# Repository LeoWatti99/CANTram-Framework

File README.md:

# CAN-TRAM-Framework
Das CAN-TRAM-Framework ist ein mikrocontrollerbasiertes, modulares Steuerungssystem, dass sich aus einzelnen Modulen zusammensetzen lässt. Die Struktur des Systems orientiert sich an üblichen SPS-Systemen, sodass eine CPU bzw. ein Hauptmodul um beliebig viele Module erweitert werden kann, um Funktionen hinzuzufügen.

## Inventor CAD Dateien öffnen
Die CAD Dateien des Projekts sind im Ordner [Inventor CAD](https://github.com/LeoWatti99/CANTram-Framework/tree/main/Inventor%20CAD)) enthalten. Um das Projekt wie vorgesehen zu öffnen muss in **Inventor 2025 oder höher** die Datei [Controller.ipj](https://github.com/LeoWatti99/CANTram-Framework/blob/main/Inventor%20CAD/Controller.ipj) geöffnet werden.

## KiCAD Schaltungen öffnen
Im Ordner [KiCad Schaltungen](https://github.com/LeoWatti99/CANTram-Framework/tree/main/KiCad%20Schaltungen) sind alle Projekte der einzelnen Platinen enthalten. Darin befinden sich sowhol Prototypen Schaltungen als auch aktuelle Modulplatinen. Um die Projekt zu öffnen wird **KiCAD 9.0.6 benötigt**. über die **.kicad_pro-Dateien** in den Unterordnern können die Projekte vollständig mit der Verlinkung zwischen Schaltplan und Layout geöffnet werden.

## C++ Framework
Die Firmware des Systems ist als C++ Bibliothek im Ordner [Framework](https://github.com/LeoWatti99/CANTram-Framework/tree/main/Framework) enthalten. 

## Dokumentation 
Die Software-Dokumentation kann [hier](https://leowatti99.github.io/CANTram-Framework/inherits.html) geöffnet werden. Sie wird automatisch durch **Doxygen** erstellt und nach Änderungen des Codes aktualisiert.

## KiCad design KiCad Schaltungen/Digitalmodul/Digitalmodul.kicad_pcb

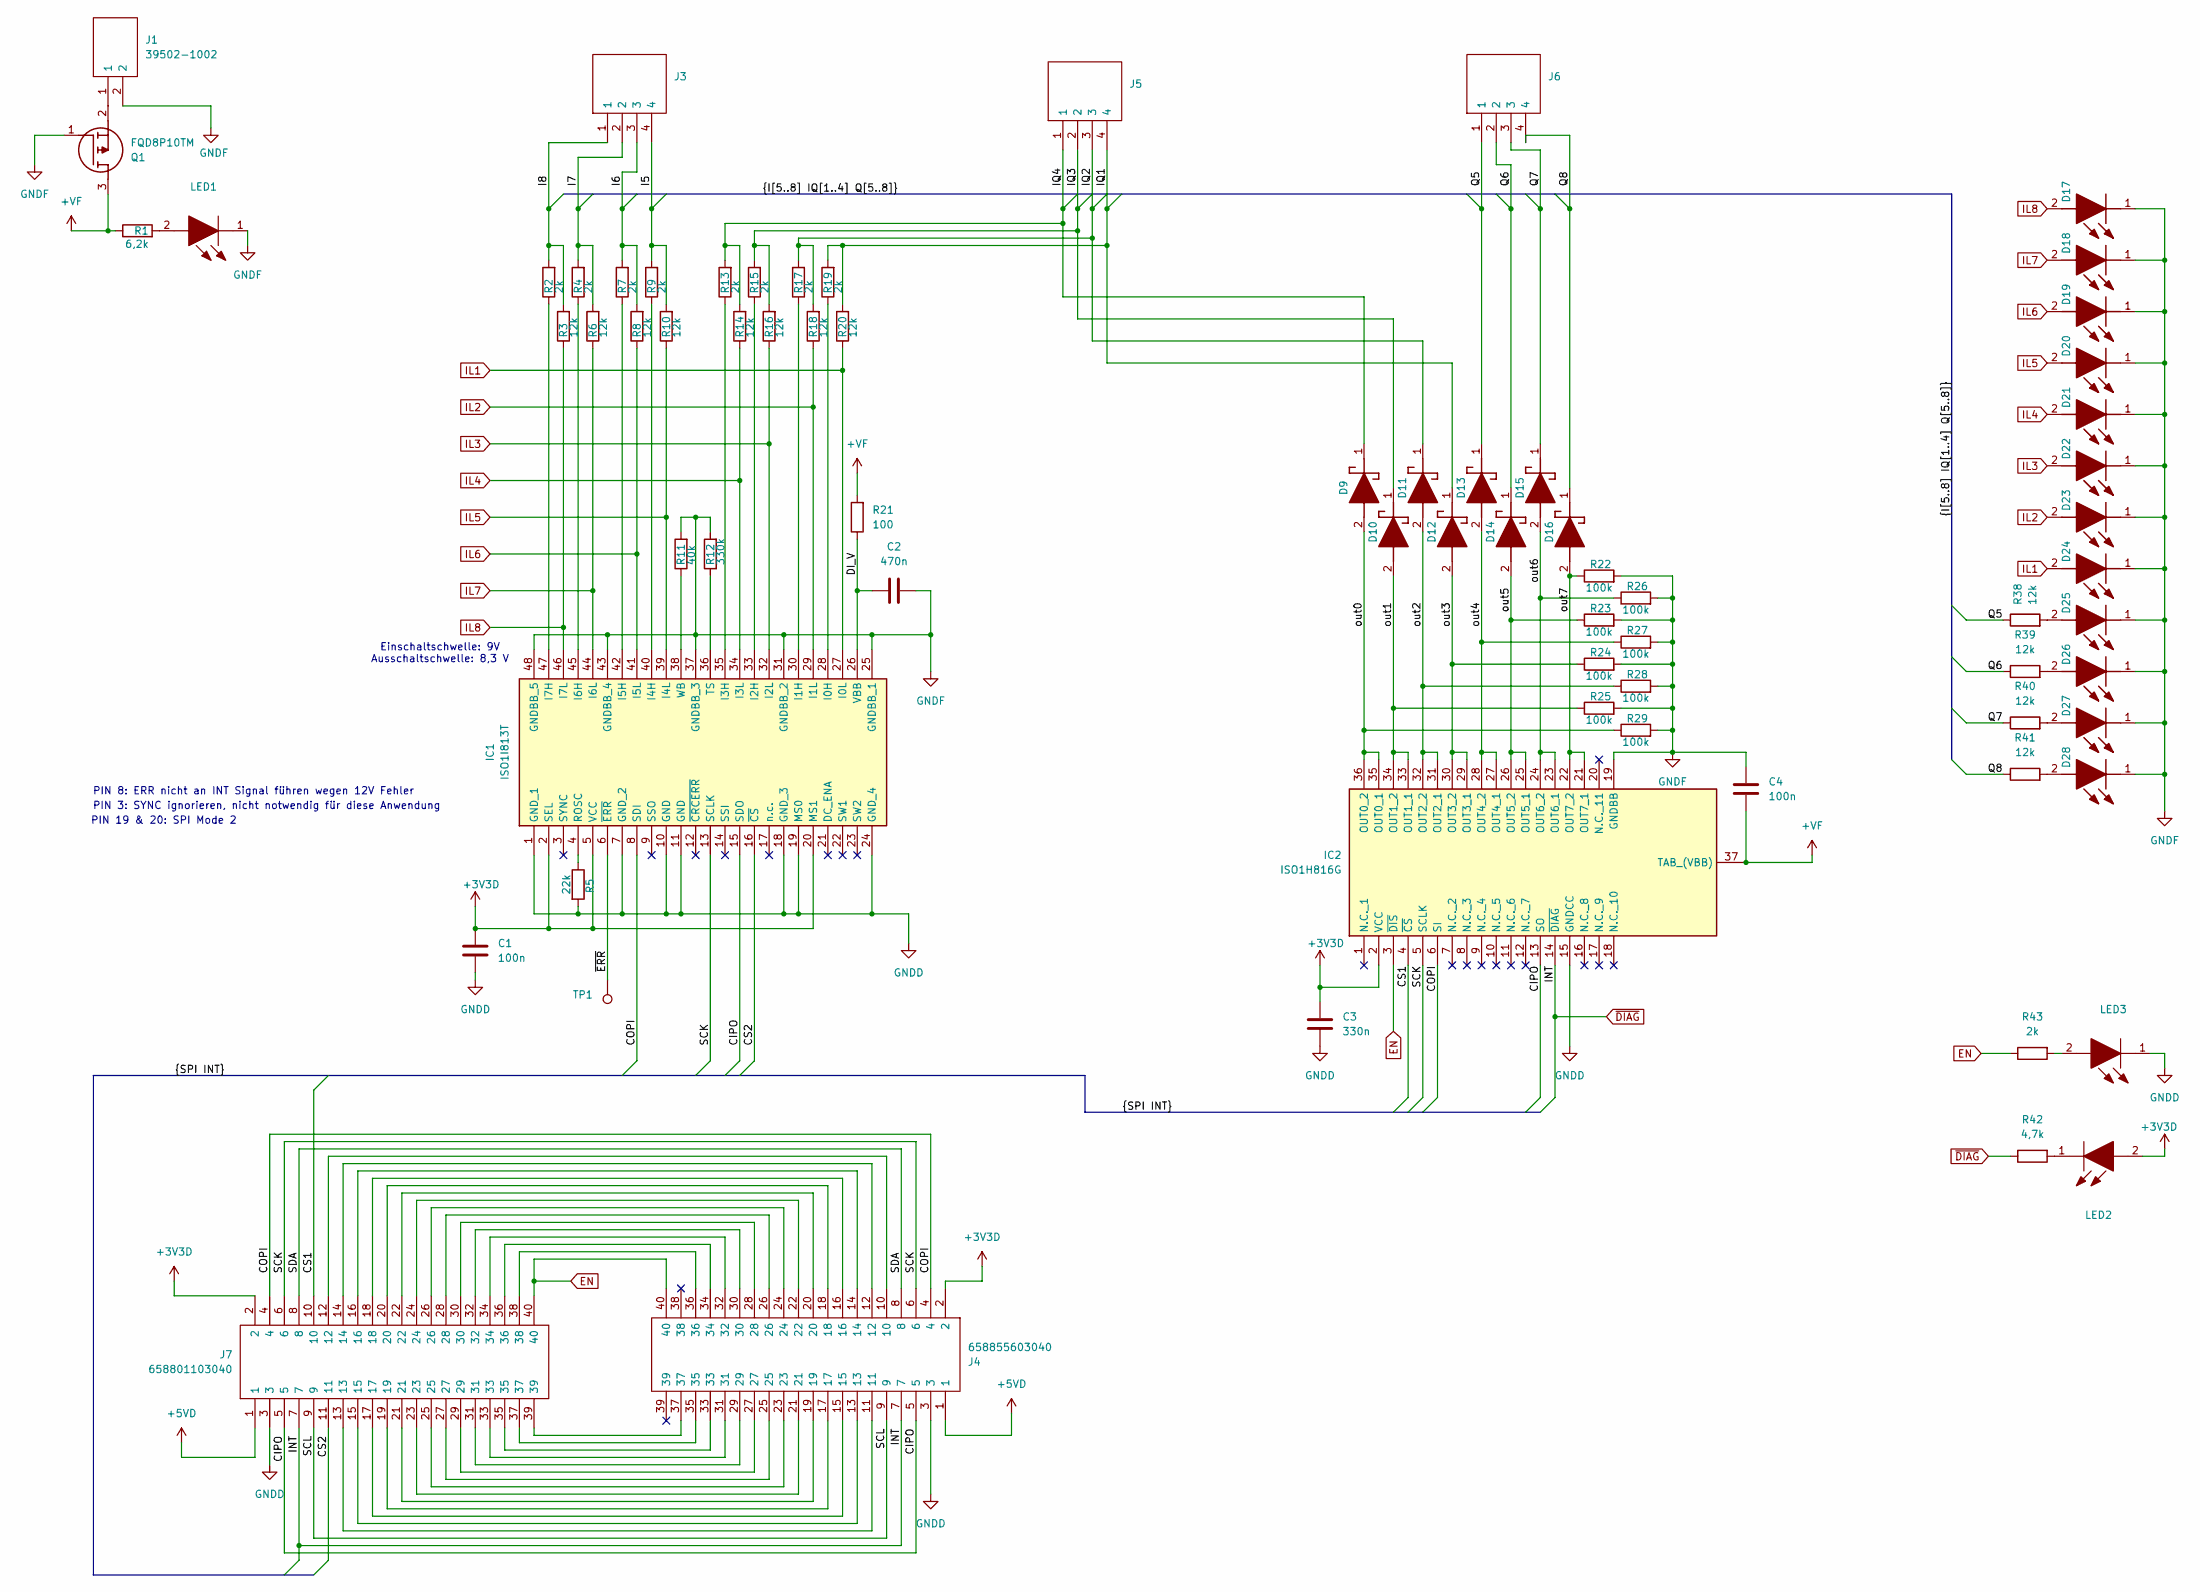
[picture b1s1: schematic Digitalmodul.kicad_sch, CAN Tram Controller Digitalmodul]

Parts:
C1, C4: 100n; C_1206_3216Metric
C2: 470n; C_1206_3216Metric
C3: 330n; C_1206_3216Metric
D9, D10, D11, D12, D13, D14, D15, D16: SS24FL; SODFL3617X108N; Mouser Part Number 512-SS24FL
D17, D18, D19, D20, D21, D22, D23, D24, D25, D26, D27, D28: 156120YS75000; LEDC5017X140N; Mouser Part Number 710-156120YS75000
IC1: ISO1I813T; SOP50P810X110-48N; Mouser Part Number 726-ISO1I813T
IC2: ISO1H816G; SOP65P1420X350-37N; Mouser Part Number 726-ISO1H816G
J1: 39502-1002; SHDR2W80P0X350_1X2_840X920X690P; Mouser Part Number 538-39502-1002
J3, J5, J6: 39502-1004; SHDRRA4W80P0X350_1X4_1540X920X730P; Mouser Part Number 538-39502-1004
J4: 658855603040; Mouser Part Number 710-658855603040
J7: 658801103040; Mouser Part Number 710-658801103040
LED1, LED3: 156120GS75000; LEDC5017X140N; Mouser Part Number 710-156120GS75000
LED2: 156120RS75000; LEDC5017X140N; Mouser Part Number 710-156120RS75000
Q1: FQD8P10TM; DPAK3-CASE-369AS; Mouser Part Number 512-FQD8P10TM
R1: 6,2k; R_1206_3216Metric; Manufacturer_Part_Number AC1206FR-076K2L; Mouser Part Number 603-AC1206FR-076K2L
R2, R4, R7, R9, R13, R15, R17, R19, R43: 2k; R_1206_3216Metric; Manufacturer_Part_Number AC1206FR-076K2L; Mouser Part Number 603-AC1206FR-076K2L
R3, R6, R8, R10, R14, R16, R18, R20, R38, R39, R40, R41: 12k; R_1206_3216Metric; Manufacturer_Part_Number AC1206FR-076K2L; Mouser Part Number 603-AC1206FR-076K2L
R5: 22k; R_1206_3216Metric; Manufacturer_Part_Number RT1206FRD0722KL; Mouser Part Number 603-RT1206FRD0722KL
R11: 40k; R_1206_3216Metric; Manufacturer_Part_Number AC1206FR-076K2L; Mouser Part Number 603-AC1206FR-076K2L
R12: 330k; R_1206_3216Metric; Manufacturer_Part_Number AC1206FR-076K2L; Mouser Part Number 603-AC1206FR-076K2L
R21: 100; R_1206_3216Metric; Manufacturer_Part_Number AC1206FR-076K2L; Mouser Part Number 603-AC1206FR-076K2L
R22, R23, R24, R25, R26, R27, R28, R29: 100k; R_1206_3216Metric; Manufacturer_Part_Number RT1206FRD0722KL; Mouser Part Number 603-RT1206FRD0722KL
R42: 4,7k; R_1206_3216Metric; Manufacturer_Part_Number AC1206FR-076K2L; Mouser Part Number 603-AC1206FR-076K2L
TP1: TestPoint; TestPoint_Pad_D2.0mm

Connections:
+3V3D: C1.1, C3.1, IC1.2 (SEL), IC1.5 (VCC), IC1.20 (MS1), IC2.2 (VCC), J4.2, J7.2, LED2.2
+5VD: J4.1, J7.1
+VF: C4.2, IC2.37 (TAB_(VBB)), Q1.3 (D), R1.1, R21.2
/CIPO: IC1.15 (SDO), IC2.13 (SO), J4.5, J7.5
/COPI: IC1.8 (SDI), IC2.6 (SI), J4.4, J7.4
/CS1: IC2.4 (~CS), J7.10
/CS2: IC1.16 (~CS), J7.11
/DI_V: C2.1, IC1.26 (VBB), R21.1
/I5: J3.4, R9.2, R10.2
/I6: J3.3, R7.2, R8.2
/I7: J3.2, R4.2, R6.2
/I8: J3.1, R2.2, R3.2
/IQ1: D12.1 (K), J5.4, R19.2, R20.2
/IQ2: D11.1 (K), J5.3, R17.2, R18.2
/IQ3: D10.1 (K), J5.2, R15.2, R16.2
/IQ4: D9.1 (K), J5.1, R13.2, R14.2
/Q5: D13.1 (K), J6.1, R38.1
/Q6: D14.1 (K), J6.2, R39.1
/Q7: D15.1 (K), J6.3, R40.1
/Q8: D16.1 (K), J6.4, R41.1
/SCK: IC1.13 (SCLK), IC2.5 (SCLK), J4.6, J7.6
/SCL: J4.9, J7.9
/SDA: J4.8, J7.8
/out0: D9.2 (A), IC2.35 (OUT0_1), IC2.36 (OUT0_2), R29.1
/out1: D10.2 (A), IC2.33 (OUT1_1), IC2.34 (OUT1_2), R25.1
/out2: D11.2 (A), IC2.31 (OUT2_1), IC2.32 (OUT2_2), R28.1
/out3: D12.2 (A), IC2.29 (OUT3_1), IC2.30 (OUT3_2), R24.1
/out4: D13.2 (A), IC2.27 (OUT4_1), IC2.28 (OUT4_2), R27.1
/out5: D14.2 (A), IC2.25 (OUT5_1), IC2.26 (OUT5_2), R23.1
/out6: D15.2 (A), IC2.23 (OUT6_1), IC2.24 (OUT6_2), R26.1
/out7: D16.2 (A), IC2.21 (OUT7_1), IC2.22 (OUT7_2), R22.1
/~ERR: IC1.6 (~ERR), TP1.1
EN: IC2.3 (~DIS), J4.40, J7.40, R43.1
GNDD: C1.2, C3.2, IC1.1 (GND_1), IC1.7 (GND_2), IC1.10 (GND), IC1.11 (GND), IC1.18 (GND_3), IC1.19 (MS0), IC1.24 (GND_4), IC2.15 (GNDCC), J4.3, J7.3, LED3.1, R5.2
GNDF: C2.2, C4.1, D17.1 (K), D18.1 (K), D19.1 (K), D20.1 (K), D21.1 (K), D22.1 (K), D23.1 (K), D24.1 (K), D25.1 (K), D26.1 (K), D27.1 (K), D28.1 (K), IC1.25 (GNDBB_1), IC1.31 (GNDBB_2), IC1.37 (GNDBB_3), IC1.43 (GNDBB_4), IC1.48 (GNDBB_5), IC2.19 (GNDBB), J1.2, LED1.1, Q1.1 (G), R11.2, R12.2, R22.2, R23.2, R24.2, R25.2, R26.2, R27.2, R28.2, R29.2
IL1: D24.2 (A), IC1.27 (I0L), R20.1
IL2: D23.2 (A), IC1.29 (I1L), R18.1
IL3: D22.2 (A), IC1.32 (I2L), R16.1
IL4: D21.2 (A), IC1.34 (I3L), R14.1
IL5: D20.2 (A), IC1.39 (I4L), R10.1
IL6: D19.2 (A), IC1.41 (I5L), R8.1
IL7: D18.2 (A), IC1.44 (I6L), R6.1
IL8: D17.2 (A), IC1.46 (I7L), R3.1
unnamed: D25.2 (A), R38.2
unnamed: D26.2 (A), R39.2
unnamed: D27.2 (A), R40.2
unnamed: D28.2 (A), R41.2
unnamed: IC1.28 (I0H), R19.1
unnamed: IC1.30 (I1H), R17.1
unnamed: IC1.33 (I2H), R15.1
unnamed: IC1.35 (I3H), R13.1
unnamed: IC1.40 (I4H), R9.1
unnamed: IC1.42 (I5H), R7.1
unnamed: IC1.45 (I6H), R4.1
unnamed: IC1.47 (I7H), R2.1
unnamed: IC1.4 (ROSC), R5.1
unnamed: IC1.36 (TS), R12.1
unnamed: IC1.38 (WB), R11.1
unnamed: J4.10, J7.12
unnamed: J4.11, J7.13
unnamed: J4.12, J7.14
unnamed: J4.13, J7.15
unnamed: J4.14, J7.16
unnamed: J4.15, J7.17
unnamed: J4.16, J7.18
unnamed: J4.17, J7.19
unnamed: J4.18, J7.20
unnamed: J4.19, J7.21
unnamed: J4.20, J7.22
unnamed: J4.21, J7.23
unnamed: J4.22, J7.24
unnamed: J4.23, J7.25
unnamed: J4.24, J7.26
unnamed: J4.25, J7.27
unnamed: J4.26, J7.28
unnamed: J4.27, J7.29
unnamed: J4.28, J7.30
unnamed: J4.29, J7.31
unnamed: J4.30, J7.32
unnamed: J4.31, J7.33
unnamed: J4.32, J7.34
unnamed: J4.33, J7.35
unnamed: J4.34, J7.36
unnamed: J4.35, J7.37
unnamed: J4.36, J7.38
unnamed: J4.37, J7.39
unnamed: LED1.2, R1.2
unnamed: LED2.1, R42.2
unnamed: LED3.2, R43.2
unnamed: J1.1, Q1.2 (S)
~DIAG: IC2.14 (~DIAG), J4.7, J7.7, R42.1

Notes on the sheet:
PIN 8: ERR nicht an INT Signal führen wegen 12V Fehler
PIN 3: SYNC ignorieren, nicht notwendig für diese Anwendung
PIN 19 & 20: SPI Mode 2
Einschaltschwelle: 9V Ausschaltschwelle: 8,3 V

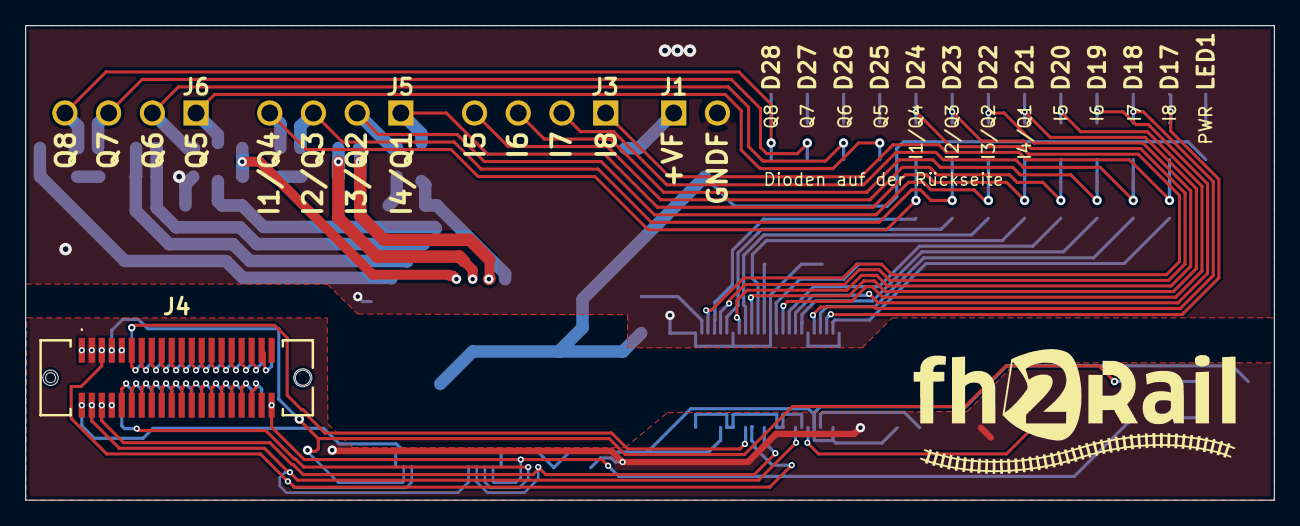
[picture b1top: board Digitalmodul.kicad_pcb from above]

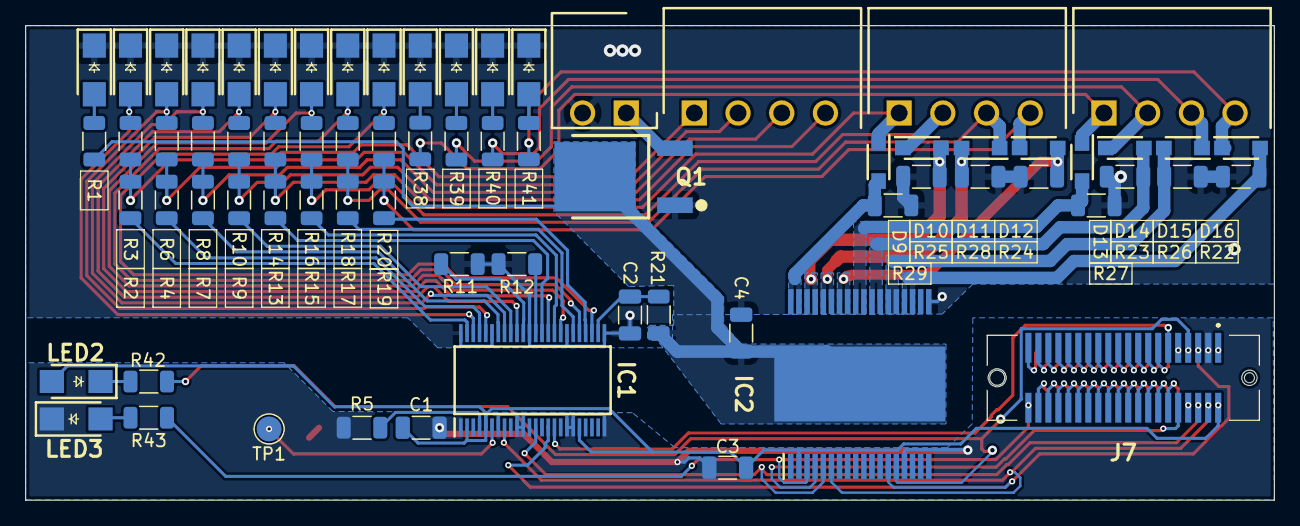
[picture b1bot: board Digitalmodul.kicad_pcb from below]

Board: 2 copper layers, 100.0 x 38.0 mm, 72 parts (71 on the bottom side), 91 nets.

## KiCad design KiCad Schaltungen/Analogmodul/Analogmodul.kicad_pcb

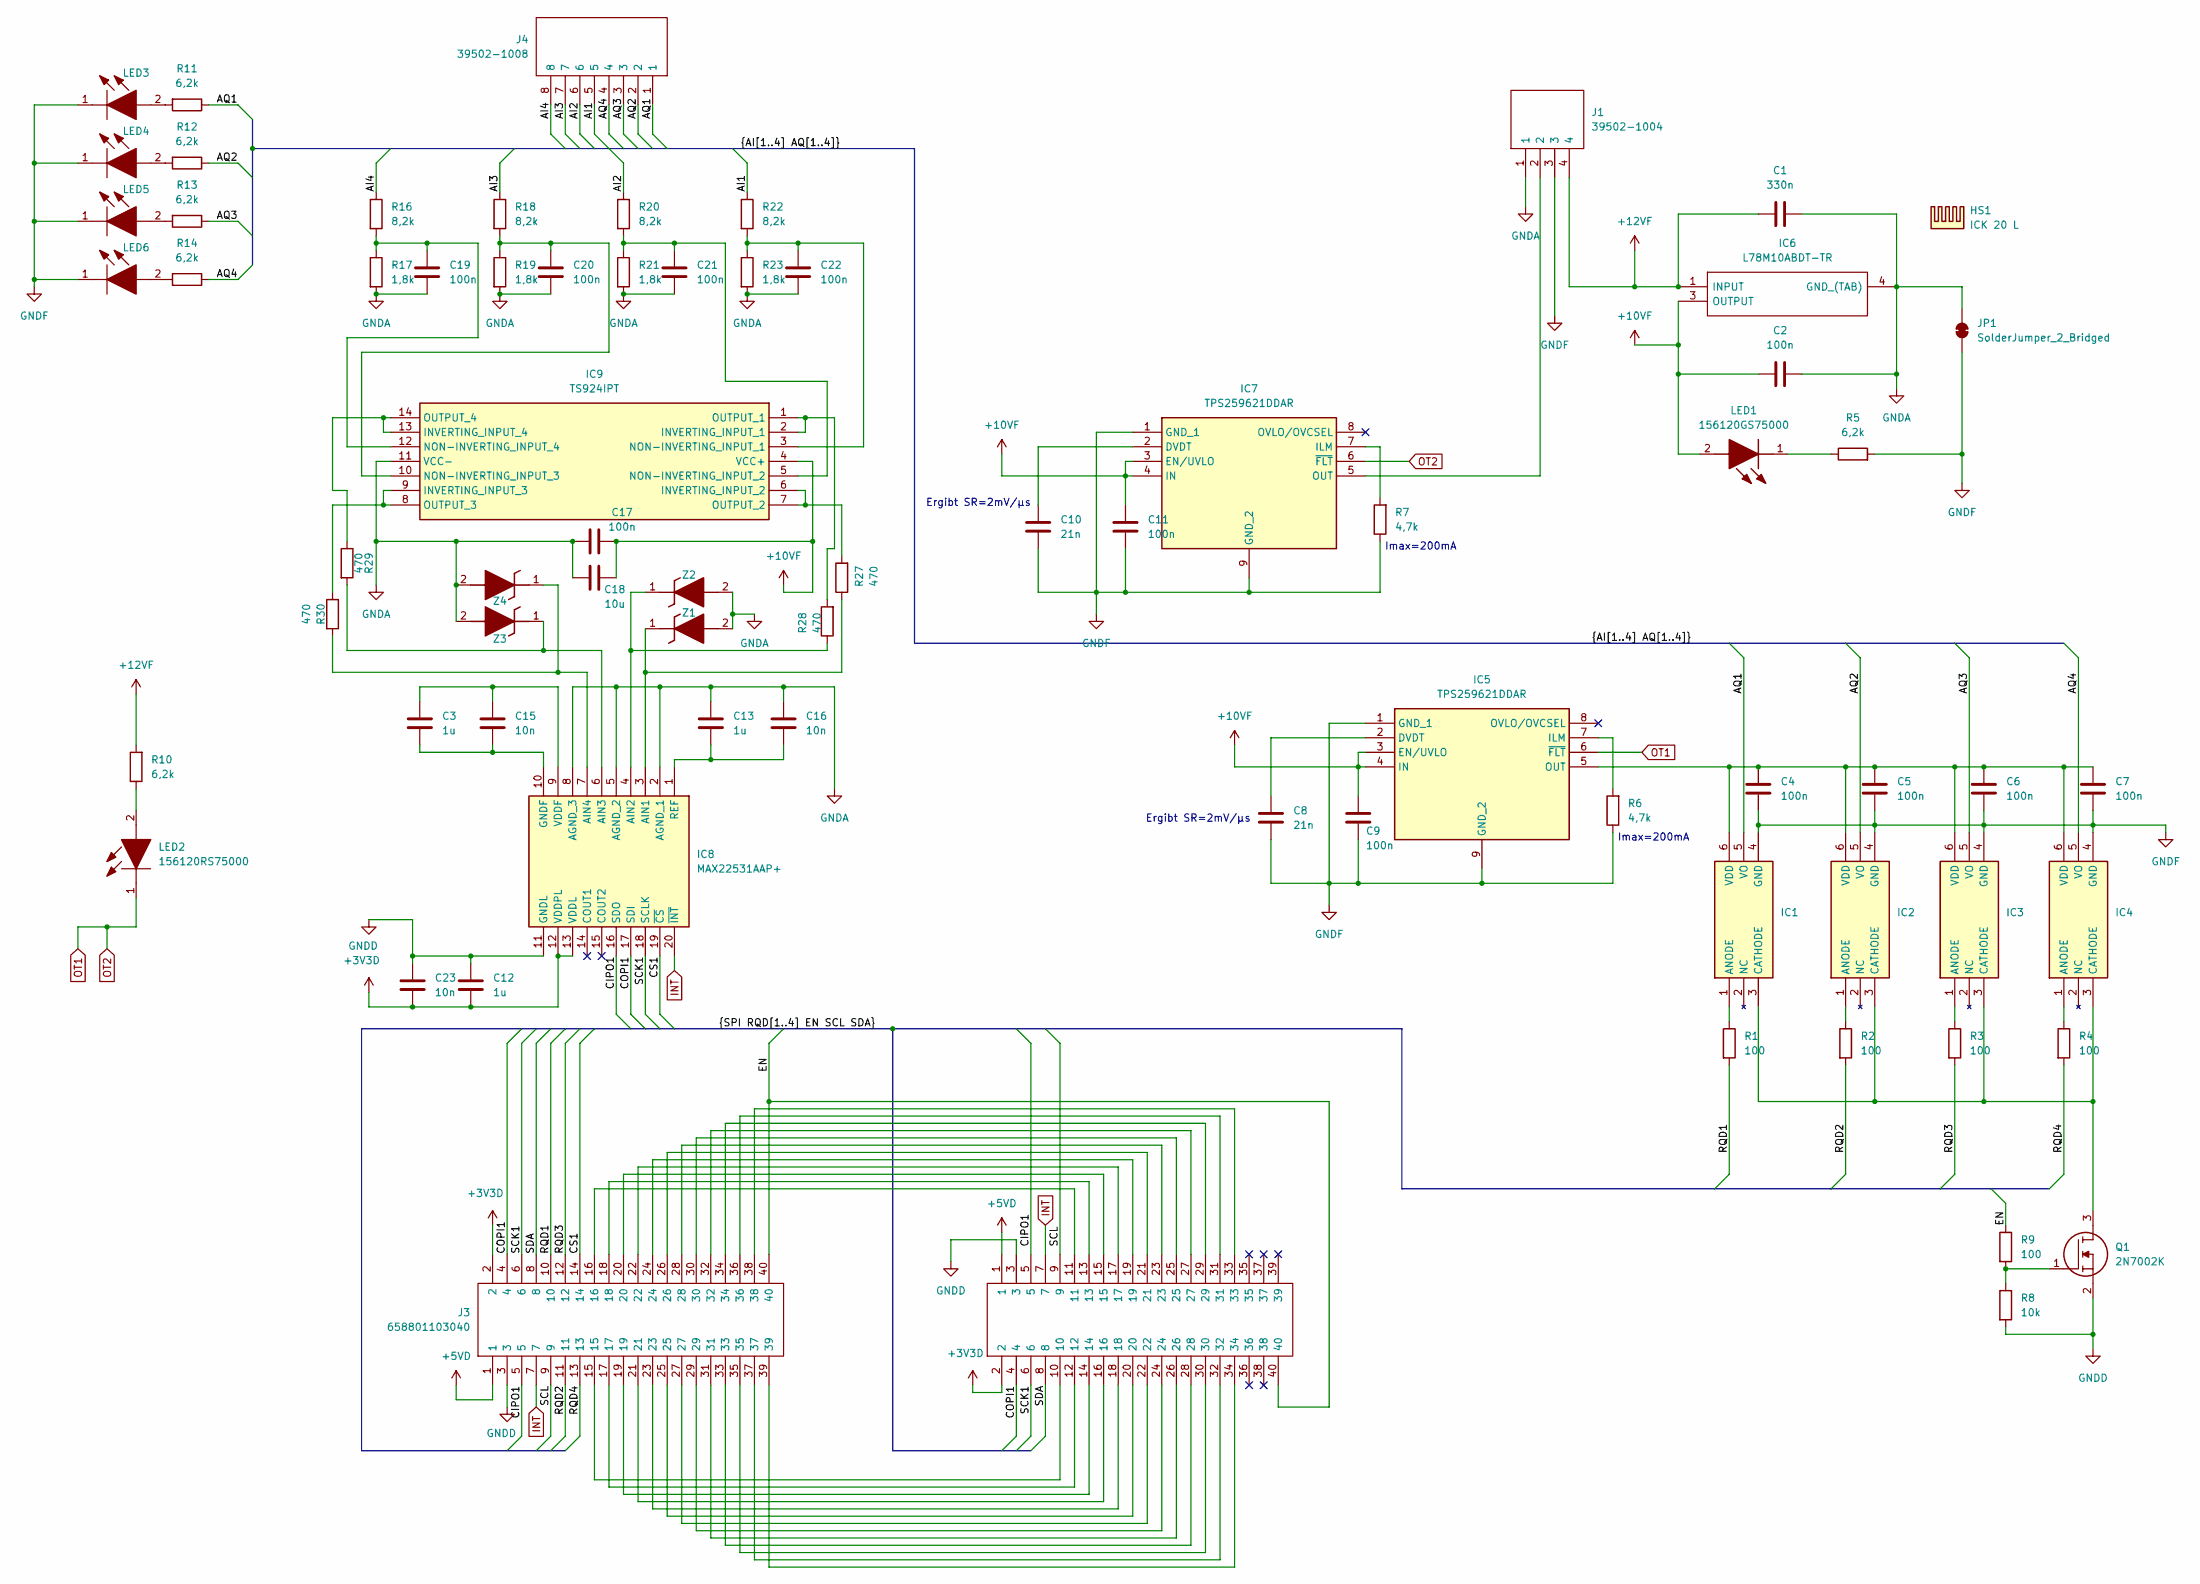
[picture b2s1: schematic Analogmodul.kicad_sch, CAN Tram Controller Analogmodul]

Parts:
C1: 330n; C_1206_3216Metric; Manufacturer_Part_Number C1206X334J1RECAUTO; Mouser Part Number 80-C1206X334J1RECAUT
C2, C4, C5, C6, C7, C9, C11: 100n; C_1206_3216Metric; Manufacturer_Part_Number GRM3195C2A104JA01D; Mouser Part Number 81-GRM3195C2A104JA1D
C3, C12, C13: 1u; C_1206_3216Metric; Manufacturer_Part_Number C1206X105J1RACTU; Mouser Part Number 80-C1206X105J1R
C8, C10: 21n; C_1206_3216Metric; Manufacturer_Part_Number GRM3195C2A104JA01D; Mouser Part Number 81-GRM3195C2A104JA1D
C15, C16, C23: 10n; C_1206_3216Metric; Manufacturer_Part_Number GRT3195C2A103JA02D; Mouser Part Number 81-GRT3195C2A103JA2D
C17: 100n; C_1206_3216Metric; Manufacturer_Part_Number GRT3195C2A103JA02D; Mouser Part Number 81-GRT3195C2A103JA2D
C18: 10u; C_1206_3216Metric; Manufacturer_Part_Number GRT3195C2A103JA02D; Mouser Part Number 81-GRT3195C2A103JA2D
C19, C20, C21, C22: 100n; C_1206_3216Metric; Manufacturer_Part_Number C1206C224J1RECAUTO; Mouser Part Number 80-C1206C224J1RECAUT
HS1: ICK 20 L; Heatsink ICK 20 L
IC1, IC2, IC3, IC4: SI8261BAD-C-ISR; SOIC127P1150X265-6N; Mouser Part Number 634-SI8261BAD-C-ISR
IC5, IC7: TPS259621DDAR; SOIC127P600X170-9N; Mouser Part Number 595-TPS259621DDAR
IC6: L78M10ABDT-TR; TO228P972X240-3N; Mouser Part Number 511-L78M10ABDT-TR
IC8: MAX22531AAP+; SOP65P778X199-20N; Mouser Part Number 700-MAX22531AAP+
IC9: TS924IPT; SOP65P640X120-14N; Mouser Part Number 511-TS924IP
J1: 39502-1004; SHDRRA4W80P0X350_1X4_1540X920X730P; Mouser Part Number 538-39502-1004
J3: 658801103040; Mouser Part Number 710-658801103040
J4: 39502-1008; SHDRRA8W80P0X350_1X8_2940X920X690P; Mouser Part Number 538-39502-1008
J6: 658855603040; Mouser Part Number 710-658855603040
JP1: SolderJumper_2_Bridged; SolderJumper-2_P1.3mm_Bridged2Bar_Pad1.0x1.5mm
LED1, LED3, LED4, LED5, LED6: 156120GS75000; LEDM3216X130N; Mouser Part Number 710-156120GS75000
LED2: 156120RS75000; LEDM3216X130N; Mouser Part Number 710-156120RS75000
Q1: 2N7002K; SOT95P240X120-3N; Mouser Part Number 512-2N7002K
R1, R2, R3, R4, R9: 100; R_1206_3216Metric; Manufacturer_Part_Number AC1206FR-07100RL; Mouser Part Number 603-AC1206FR-07100RL
R5, R10, R11, R12, R13, R14: 6,2k; R_1206_3216Metric; Manufacturer_Part_Number AC1206FR-076K2L; Mouser Part Number 603-AC1206FR-076K2L
R6, R7: 4,7k; R_1206_3216Metric; Manufacturer_Part_Number AC1206FR-07100RL; Mouser Part Number 603-AC1206FR-07100RL
R8: 10k; R_1206_3216Metric; Manufacturer_Part_Number AC1206FR-07100RL; Mouser Part Number 603-AC1206FR-07100RL
R16, R18, R20, R22: 8,2k; R_1206_3216Metric; Manufacturer_Part_Number CRGCQ1206F8K2; Mouser Part Number 279-CRGCQ1206F8K2
R17, R19, R21, R23: 1,8k; R_1206_3216Metric; Manufacturer_Part_Number CRCW12061K80FKEAC; Mouser Part Number 71-CRCW12061K80FKEAC
R27, R28, R29, R30: 470; R_1206_3216Metric; Manufacturer_Part_Number CRGCQ1206F8K2; Mouser Part Number 279-CRGCQ1206F8K2
Z1, Z2, Z3, Z4: SZMMSZ4679T1G; SOD3716X135N; Mouser Part Number 863-SZMMSZ4679T1G

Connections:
+3V3D: C12.1, C23.1, IC8.12 (VDDPL), IC8.13 (VDDL), J3.2, J6.2
+5VD: J3.1, J6.1
+10VF: C2.1, C9.2, C11.2, C17.2, C18.2, IC5.3 (EN/UVLO), IC5.4 (IN), IC6.3 (OUTPUT), IC7.3 (EN/UVLO), IC7.4 (IN), IC9.4 (VCC+), LED1.2 (A)
+12VF: C1.1, IC6.1 (INPUT), J1.4, R10.2
/AI1: J4.5, R22.1
/AI2: J4.6, R20.1
/AI3: J4.7, R18.1
/AI4: J4.8, R16.1
/AQ1: IC1.5 (VO), J4.1, R11.1
/AQ2: IC2.5 (VO), J4.2, R12.1
/AQ3: IC3.5 (VO), J4.3, R13.1
/AQ4: IC4.5 (VO), J4.4, R14.1
/CIPO1: IC8.16 (SDO), J3.5, J6.5
/COPI1: IC8.17 (SDI), J3.4, J6.4
/CS1: IC8.19 (~CS), J3.14
/EN: J3.40, J6.40, R9.1
/RQD1: J3.10, R1.2
/RQD2: J3.11, R2.2
/RQD3: J3.12, R3.2
/RQD4: J3.13, R4.2
/SCK1: IC8.18 (SCLK), J3.6, J6.6
/SCL: J3.9, J6.9
/SDA: J3.8, J6.8
GNDA: C1.2, C2.2, C13.1, C16.1, C17.1, C18.1, C19.2, C20.2, C21.2, C22.2, IC6.4 (GND_(TAB)), IC8.2 (AGND_1), IC8.5 (AGND_2), IC8.8 (AGND_3), IC9.11 (VCC-), J1.1, JP1.2 (B), R17.2, R19.2, R21.2, R23.2, Z1.2 (A), Z2.2 (A), Z3.2 (A), Z4.2 (A)
GNDD: C12.2, C23.2, IC8.11 (GNDL), J3.3, J6.3, Q1.2, R8.2
GNDF: C4.1, C5.1, C6.1, C7.1, C8.2, C9.1, C10.2, C11.1, IC1.4 (GND), IC2.4 (GND), IC3.4 (GND), IC4.4 (GND), IC5.1 (GND_1), IC5.9 (GND_2), IC7.1 (GND_1), IC7.9 (GND_2), J1.3, JP1.1 (A), LED3.1, LED4.1, LED5.1, LED6.1, R5.2, R6.1, R7.1
INT: IC8.20 (~INT), J3.7, J6.7
unnamed: IC1.1 (ANODE), R1.1
unnamed: IC1.3 (CATHODE), IC2.3 (CATHODE), IC3.3 (CATHODE), IC4.3 (CATHODE), Q1.3
unnamed: C4.2, C5.2, C6.2, C7.2, IC1.6 (VDD), IC2.6 (VDD), IC3.6 (VDD), IC4.6 (VDD), IC5.5 (OUT)
unnamed: IC2.1 (ANODE), R2.1
unnamed: IC3.1 (ANODE), R3.1
unnamed: IC4.1 (ANODE), R4.1
unnamed: C8.1, IC5.2 (DVDT)
unnamed: IC5.7 (ILM), R6.2
unnamed: C10.1, IC7.2 (DVDT)
unnamed: IC7.7 (ILM), R7.2
unnamed: IC7.5 (OUT), J1.2
unnamed: IC8.3 (AIN1), R27.1, Z1.1 (K)
unnamed: IC8.4 (AIN2), R28.1, Z2.1 (K)
unnamed: IC8.6 (AIN3), R29.2, Z3.1 (K)
unnamed: IC8.7 (AIN4), R30.2, Z4.1 (K)
unnamed: C3.2, C15.2, IC8.10 (GNDF)
unnamed: C13.2, C16.2, IC8.1 (REF)
unnamed: C3.1, C15.1, IC8.9 (VDDF)
unnamed: IC9.1 (OUTPUT_1), IC9.2 (INVERTING_INPUT_1), R28.2
unnamed: IC9.6 (INVERTING_INPUT_2), IC9.7 (OUTPUT_2), R27.2
unnamed: IC9.8 (OUTPUT_3), IC9.9 (INVERTING_INPUT_3), R30.1
unnamed: IC9.13 (INVERTING_INPUT_4), IC9.14 (OUTPUT_4), R29.1
unnamed: C22.1, IC9.3 (NON-INVERTING_INPUT_1), R22.2, R23.1
unnamed: C21.1, IC9.5 (NON-INVERTING_INPUT_2), R20.2, R21.1
unnamed: C20.1, IC9.10 (NON-INVERTING_INPUT_3), R18.2, R19.1
unnamed: C19.1, IC9.12 (NON-INVERTING_INPUT_4), R16.2, R17.1
unnamed: J3.15, J6.10
unnamed: J3.16, J6.11
unnamed: J3.17, J6.12
unnamed: J3.18, J6.13
unnamed: J3.19, J6.14
unnamed: J3.20, J6.15
unnamed: J3.21, J6.16
unnamed: J3.22, J6.17
unnamed: J3.23, J6.18
unnamed: J3.24, J6.19
unnamed: J3.25, J6.20
unnamed: J3.26, J6.21
unnamed: J3.27, J6.22
unnamed: J3.28, J6.23
unnamed: J3.29, J6.24
unnamed: J3.30, J6.25
unnamed: J3.31, J6.26
unnamed: J3.32, J6.27
unnamed: J3.33, J6.28
unnamed: J3.34, J6.29
unnamed: J3.35, J6.30
unnamed: J3.36, J6.31
unnamed: J3.37, J6.32
unnamed: J3.38, J6.33
unnamed: J3.39, J6.34
unnamed: LED1.1 (K), R5.1
unnamed: LED2.2, R10.1
unnamed: LED3.2, R11.2
unnamed: LED4.2, R12.2
unnamed: LED5.2, R13.2
unnamed: LED6.2, R14.2
unnamed: Q1.1, R8.1, R9.2
OT1: IC5.6 (~FLT), IC7.6 (~FLT), LED2.1

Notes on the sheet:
Imax=200mA
Ergibt SR=2mV/µs

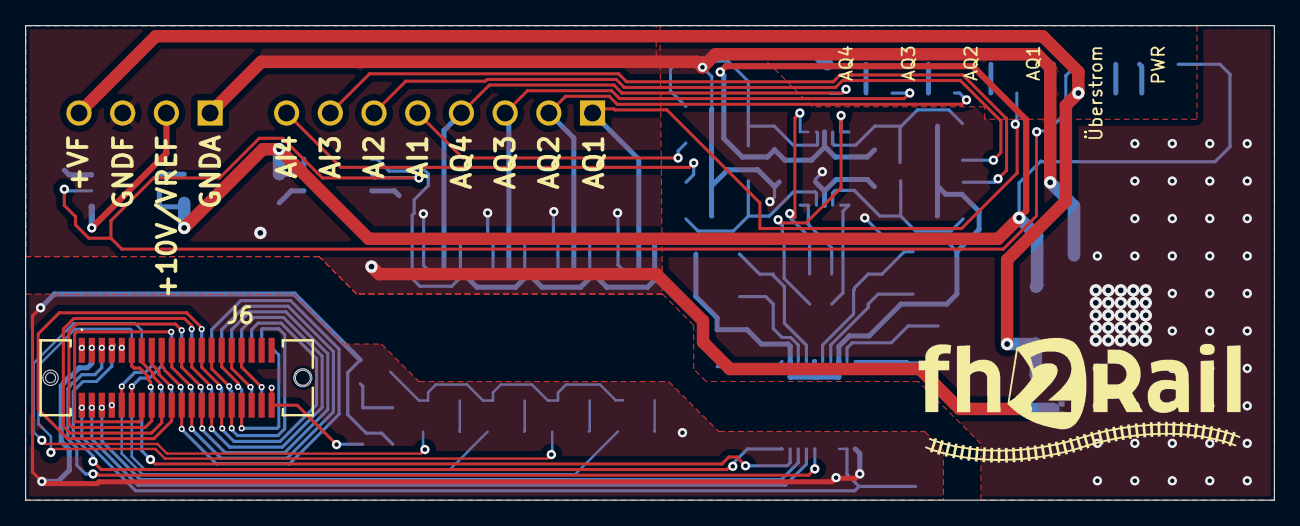
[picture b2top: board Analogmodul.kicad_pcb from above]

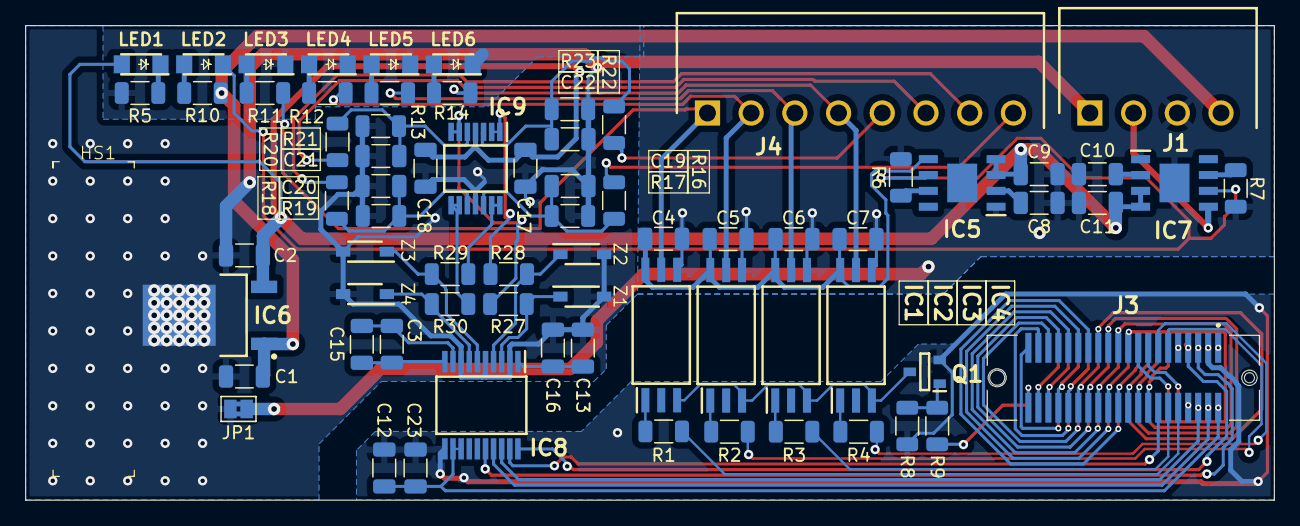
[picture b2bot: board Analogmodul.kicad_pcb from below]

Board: 2 copper layers, 100.0 x 38.0 mm, 74 parts (73 on the bottom side), 86 nets.

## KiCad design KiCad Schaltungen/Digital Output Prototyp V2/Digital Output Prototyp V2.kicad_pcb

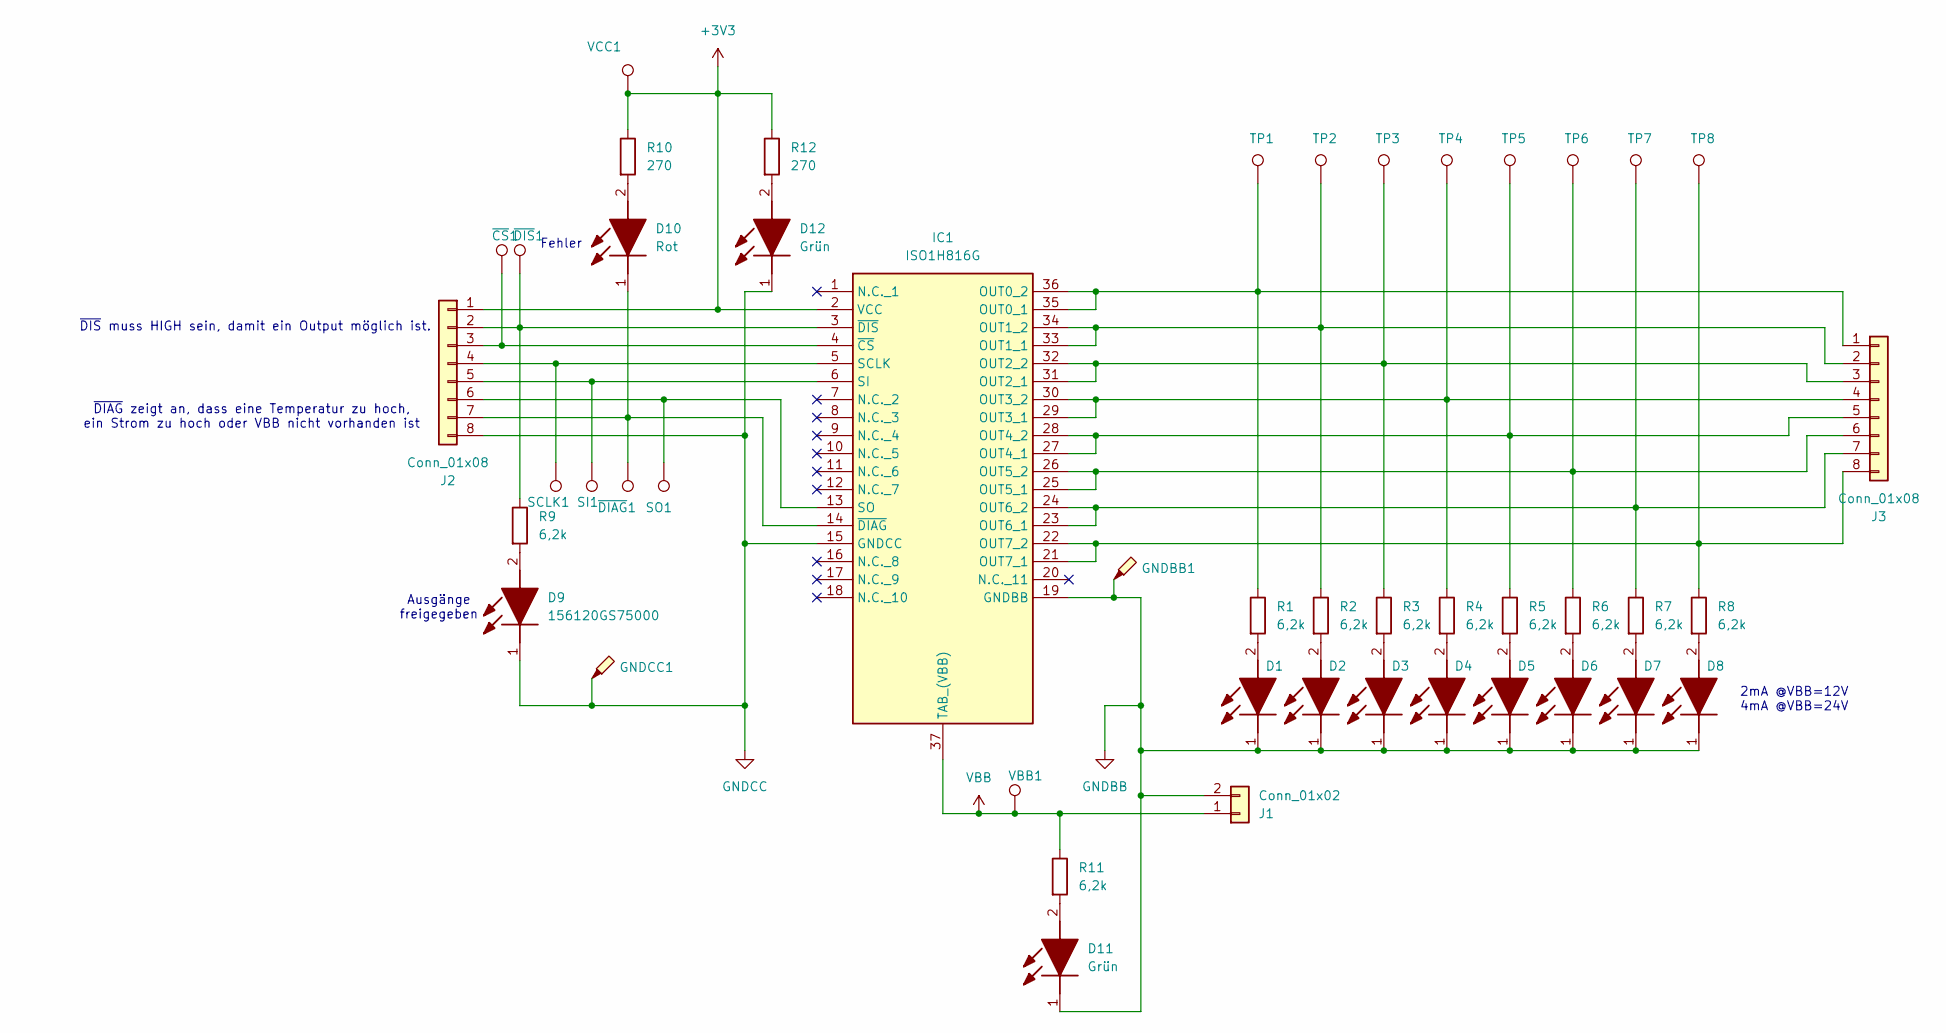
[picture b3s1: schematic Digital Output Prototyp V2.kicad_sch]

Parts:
D1, D2, D3, D4, D5, D6, D7, D8: 156120YS75000; LEDC5017X140N; Mouser Part Number 710-156120YS75000
D9: 156120GS75000; LEDC5017X140N; Mouser Part Number 710-156120GS75000
D10: Rot; LEDC5017X140N; Mouser Part Number 710-156120RS75000
D11, D12: Grün; LEDC5017X140N; Mouser Part Number 710-156120GS75000
GNDBB1: TestPoint_Probe; TestPoint_Keystone_5000-5004_Miniature; Manufacturer_Part_Number 5001; Mouser Part Number 534-5001
GNDCC1: TestPoint_Probe; TestPoint_Keystone_5000-5004_Miniature; Manufacturer_Part_Number 5001; Mouser Part Number 534-5001
IC1: ISO1H816G; SOP65P1420X350-37N; Mouser Part Number 726-ISO1H816G
J1: Conn_01x02; PinSocket_1x02_P2.54mm_Vertical
J2, J3: Conn_01x08; PinSocket_1x08_P2.54mm_Vertical
R1, R2, R3, R4, R5, R6, R7, R8, R9, R11: 6,2k; R_1206_3216Metric; Manufacturer_Part_Number AC1206FR-076K2L; Mouser Part Number 603-AC1206FR-076K2L
R10, R12: 270; R_1206_3216Metric; Mouser Part Number 603-RT1206FRE07270RL
SCLK1: TestPoint; TestPoint_Pad_D2.0mm
SI1: TestPoint; TestPoint_Pad_D2.0mm
SO1: TestPoint; TestPoint_Pad_D2.0mm
TP1, TP2, TP3, TP4, TP5, TP6, TP7, TP8: TestPoint; TestPoint_Pad_D2.0mm
VBB1: TestPoint; TestPoint_Pad_D2.0mm
VCC1: TestPoint; TestPoint_Pad_D2.0mm
~{CS}1: TestPoint; TestPoint_Pad_D2.0mm
~{DIAG}1: TestPoint; TestPoint_Pad_D2.0mm
~{DIS}1: TestPoint; TestPoint_Pad_D2.0mm

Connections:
+3V3: IC1.2 (VCC), J2.1, R10.1, R12.1, VCC1.1
GNDBB: D1.1 (K), D2.1 (K), D3.1 (K), D4.1 (K), D5.1 (K), D6.1 (K), D7.1 (K), D8.1 (K), D11.1 (K), GNDBB1.1, IC1.19 (GNDBB), J1.2
GNDCC: D9.1 (K), D12.1 (K), GNDCC1.1, IC1.15 (GNDCC), J2.8
unnamed: D1.2 (A), R1.2
unnamed: D2.2 (A), R2.2
unnamed: D3.2 (A), R3.2
unnamed: D4.2 (A), R4.2
unnamed: D5.2 (A), R5.2
unnamed: D6.2 (A), R6.2
unnamed: D7.2 (A), R7.2
unnamed: D8.2 (A), R8.2
unnamed: D9.2 (A), R9.2
unnamed: D10.2 (A), R10.2
unnamed: D10.1 (K), IC1.14 (~DIAG), J2.7, ~{DIAG}1.1
unnamed: D11.2 (A), R11.2
unnamed: D12.2 (A), R12.2
unnamed: IC1.35 (OUT0_1), IC1.36 (OUT0_2), J3.1, R1.1, TP1.1
unnamed: IC1.33 (OUT1_1), IC1.34 (OUT1_2), J3.2, R2.1, TP2.1
unnamed: IC1.31 (OUT2_1), IC1.32 (OUT2_2), J3.3, R3.1, TP3.1
unnamed: IC1.29 (OUT3_1), IC1.30 (OUT3_2), J3.4, R4.1, TP4.1
unnamed: IC1.27 (OUT4_1), IC1.28 (OUT4_2), J3.5, R5.1, TP5.1
unnamed: IC1.25 (OUT5_1), IC1.26 (OUT5_2), J3.6, R6.1, TP6.1
unnamed: IC1.23 (OUT6_1), IC1.24 (OUT6_2), J3.7, R7.1, TP7.1
unnamed: IC1.21 (OUT7_1), IC1.22 (OUT7_2), J3.8, R8.1, TP8.1
unnamed: IC1.5 (SCLK), J2.4, SCLK1.1
unnamed: IC1.6 (SI), J2.5, SI1.1
unnamed: IC1.13 (SO), J2.6, SO1.1
unnamed: IC1.4 (~CS), J2.3, ~{CS}1.1
unnamed: IC1.3 (~DIS), J2.2, R9.1, ~{DIS}1.1
VBB: IC1.37 (TAB_(VBB)), J1.1, R11.1, VBB1.1

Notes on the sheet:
Fehler
~{DIAG} zeigt an, dass eine Temperatur zu hoch, ein Strom zu hoch oder VBB nicht vorhanden ist
~{DIS} muss HIGH sein, damit ein Output möglich ist.
2mA @VBB=12V 4mA @VBB=24V
Ausgänge freigegeben

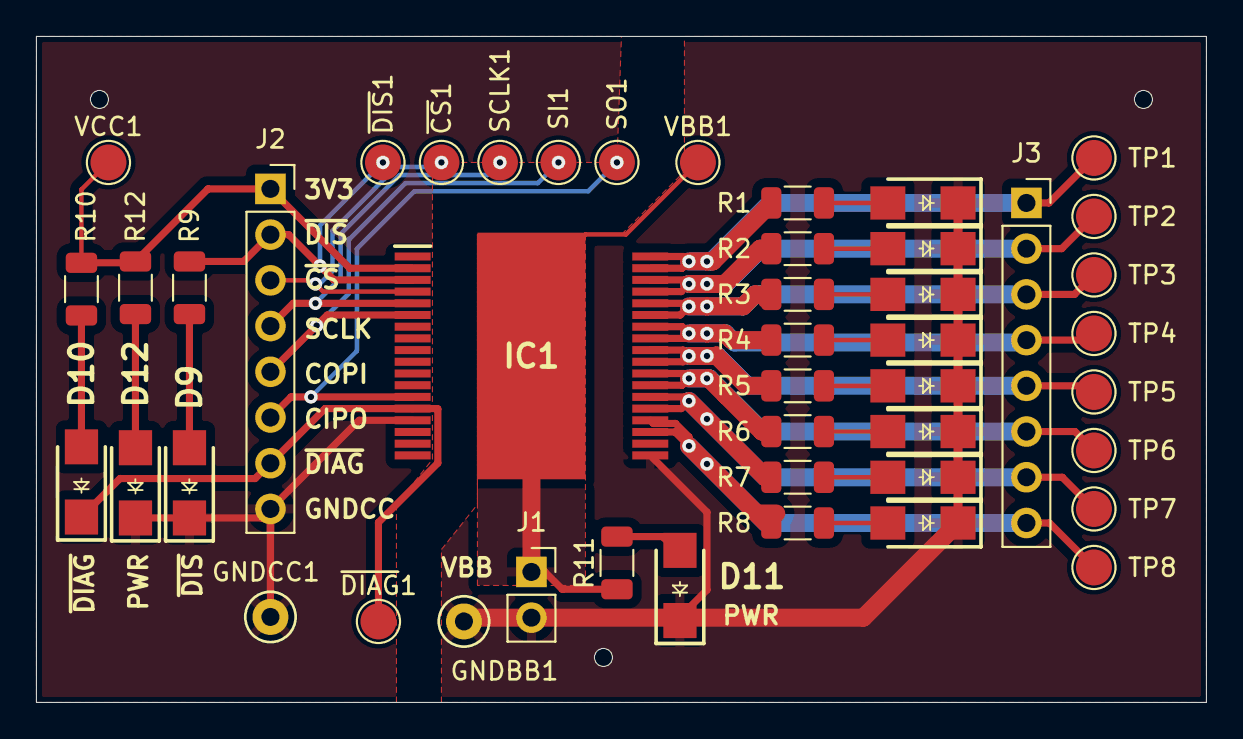
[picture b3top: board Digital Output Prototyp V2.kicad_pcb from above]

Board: 2 copper layers, 65.0 x 37.0 mm, 43 parts (0 on the bottom side), 30 nets.
